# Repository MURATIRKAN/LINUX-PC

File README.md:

# LINUX-PC
DEBIAN İMAGE DOSYA:https://www.beagleboard.org/distros/am335x-debian-11-7-2023-08-05-4gb-emmc-iot-flasher
COUNTER STRIKE VE MINECRAFT APK ANDROID SÜRÜMLERİ İLE ÇALIŞIR.

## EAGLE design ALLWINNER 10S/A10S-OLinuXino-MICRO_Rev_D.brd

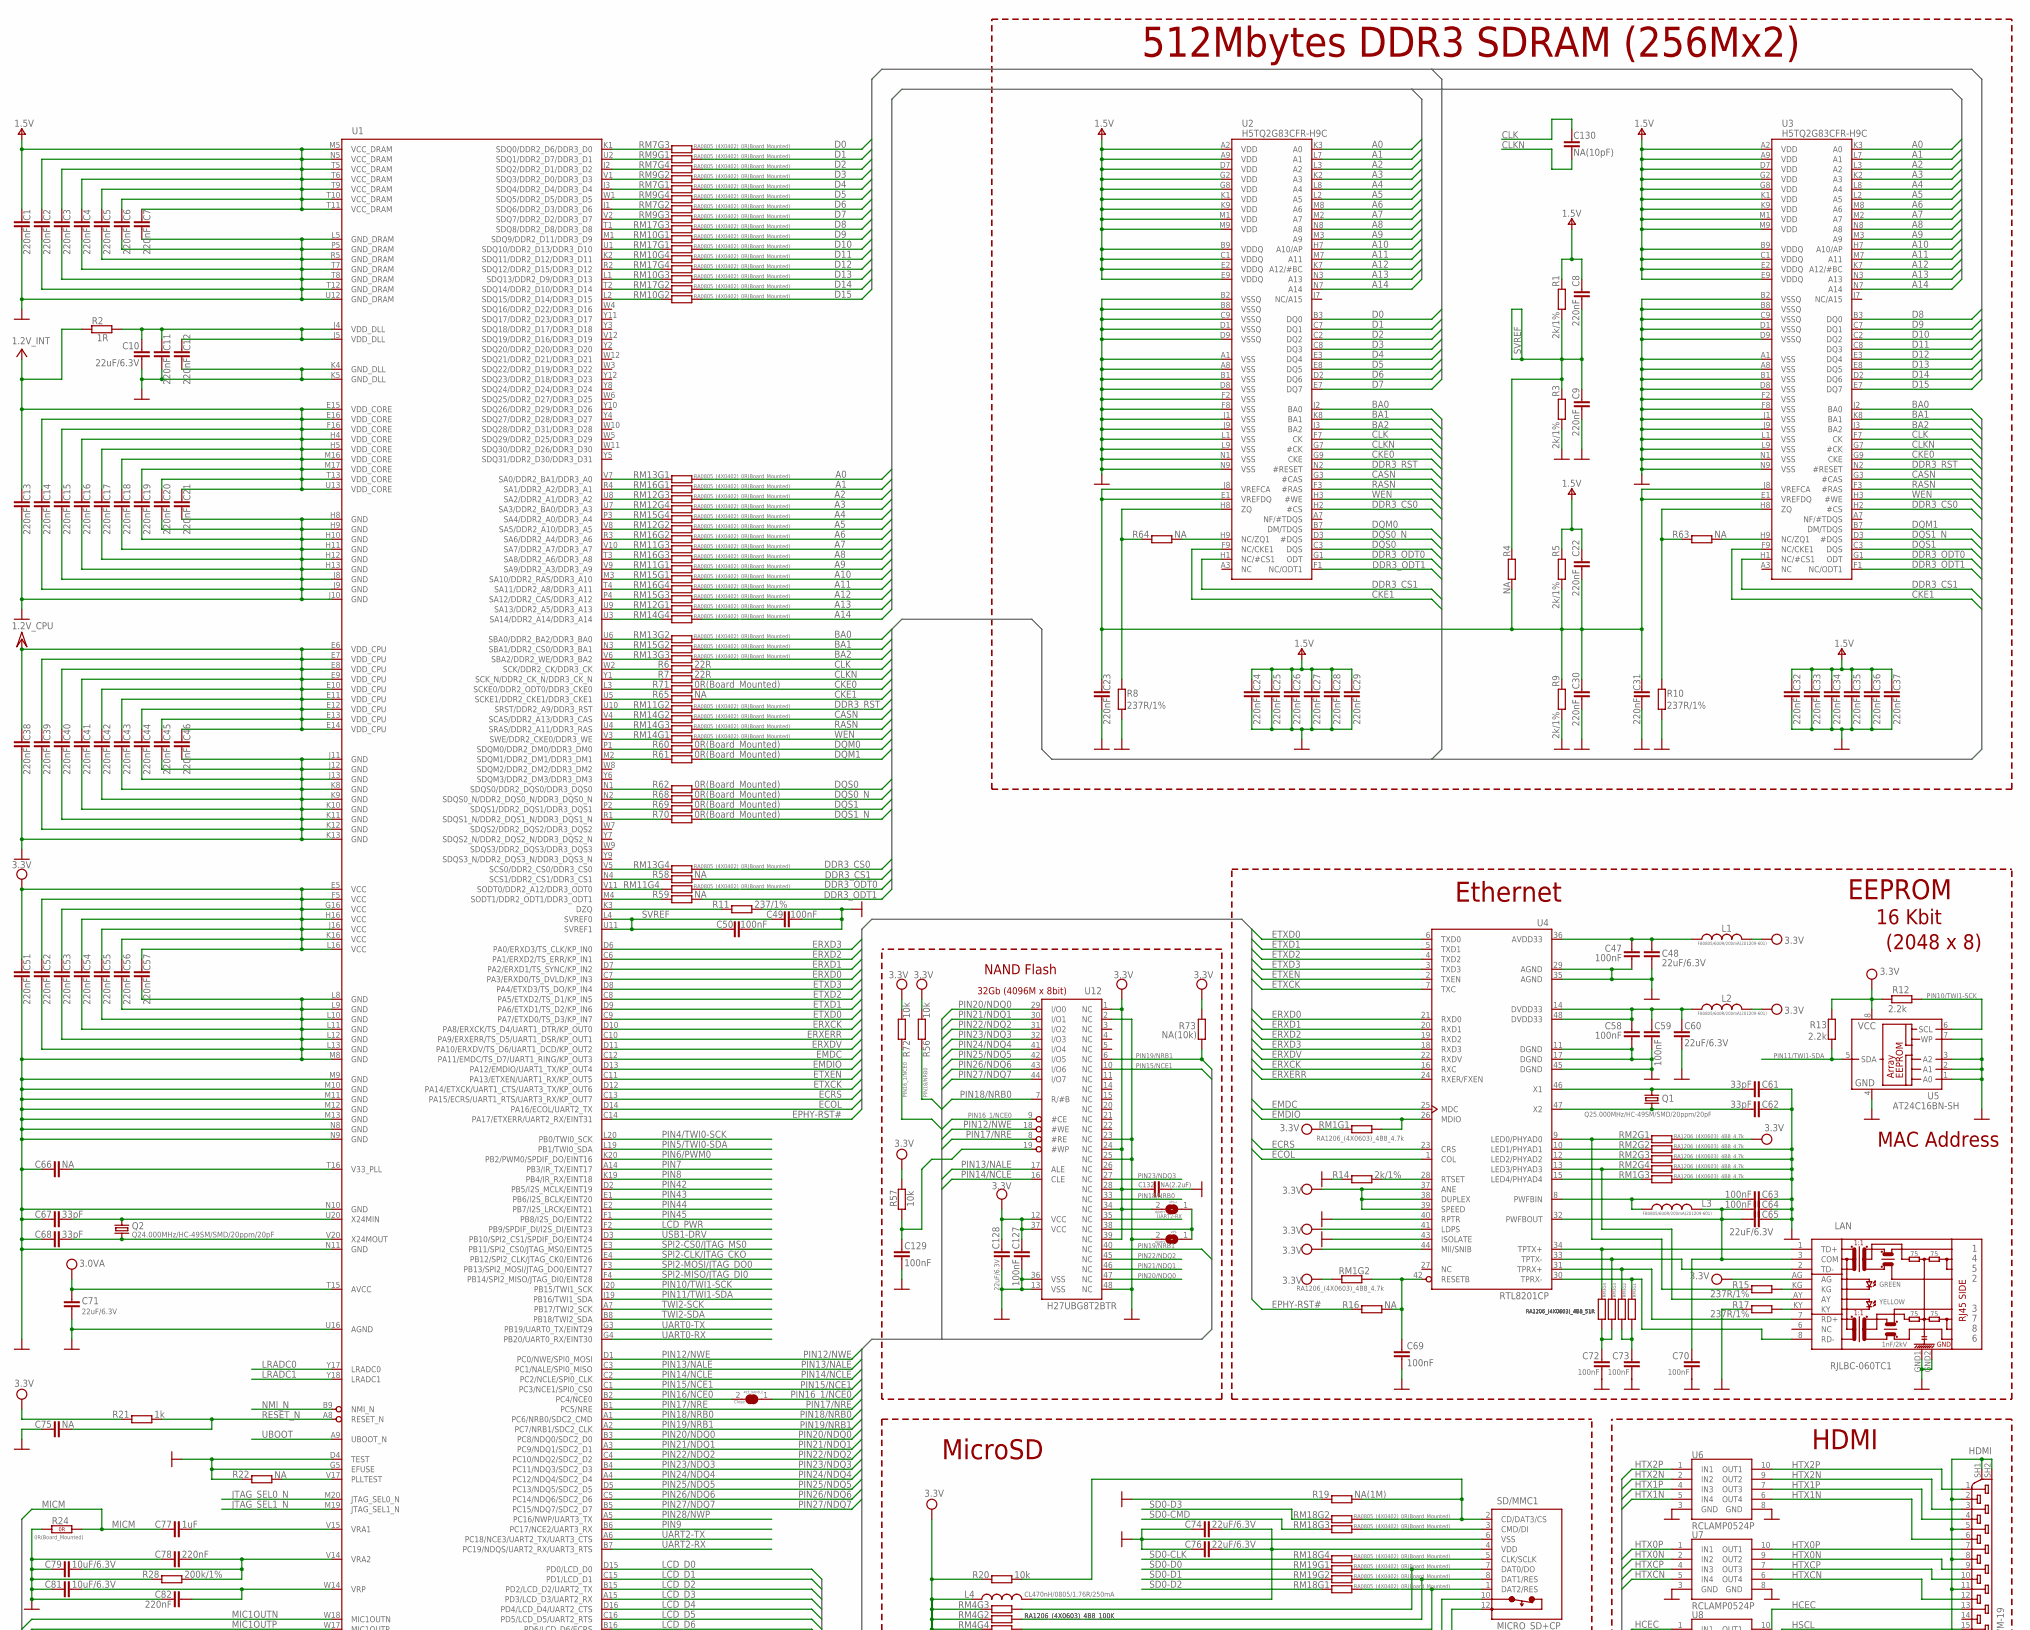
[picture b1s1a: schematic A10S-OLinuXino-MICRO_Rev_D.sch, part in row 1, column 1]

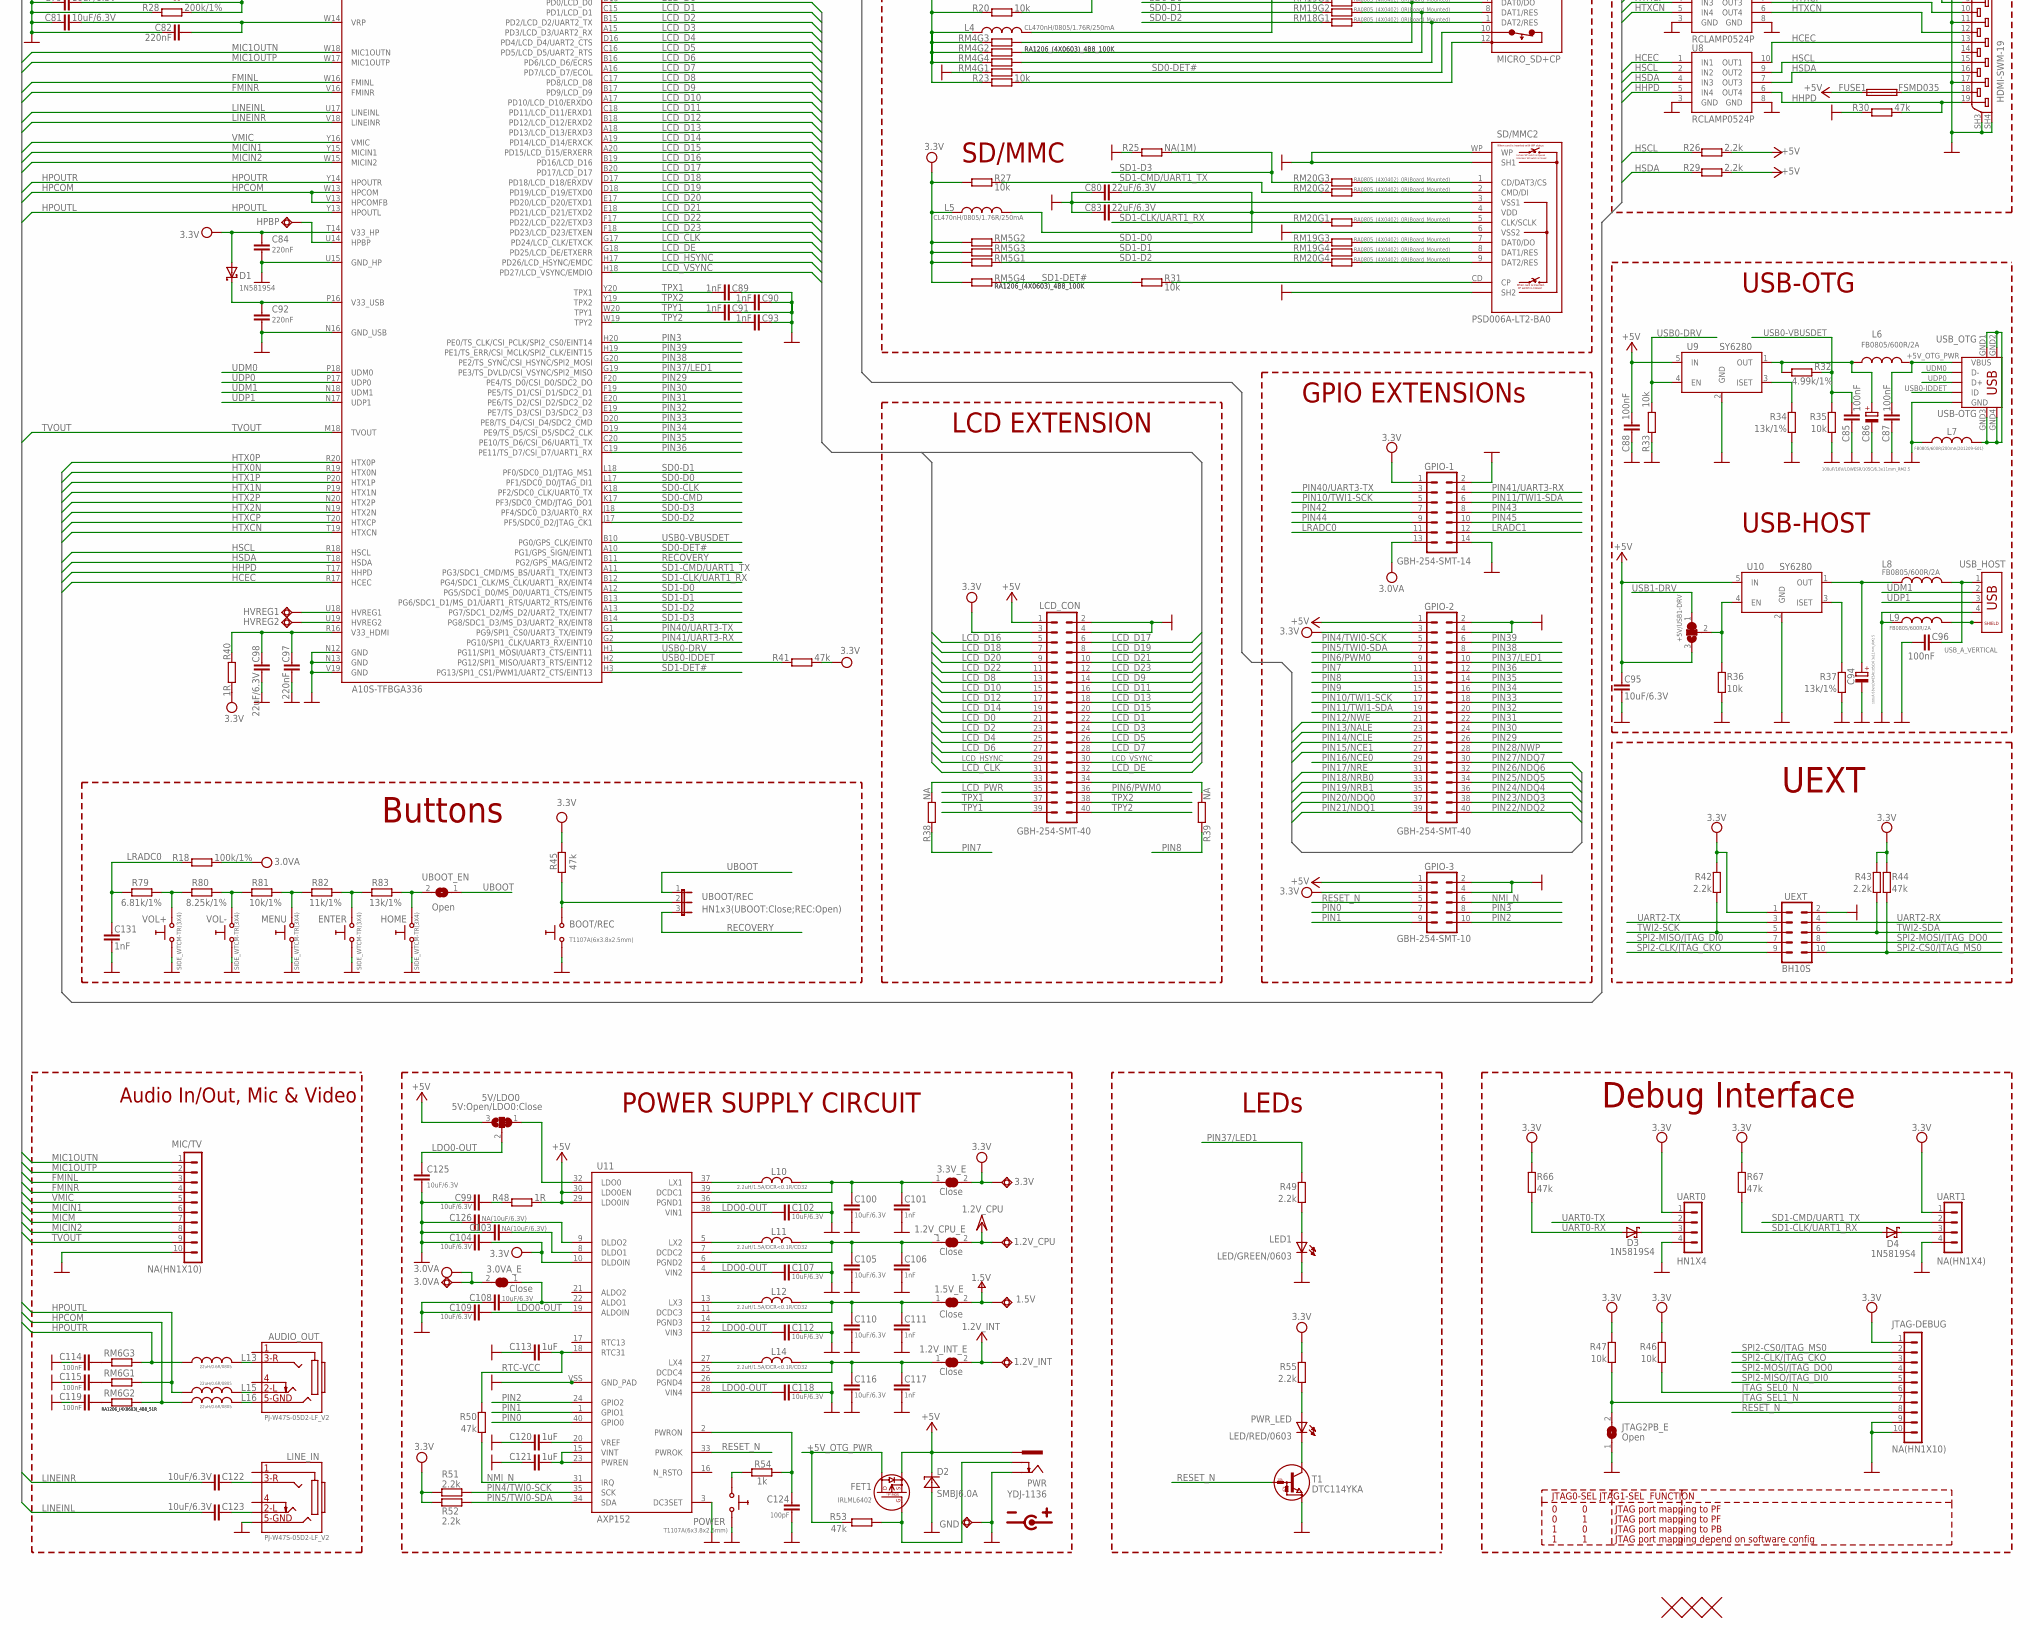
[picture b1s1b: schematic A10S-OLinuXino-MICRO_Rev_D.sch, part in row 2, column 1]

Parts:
1.2V_CPU, 1.2V_INT, 1.5V, 3.0VA, 3.3V: TESTPADTESTPAD_40-ROUND; TESTPAD_40-ROUND
1.2V_CPU_E, 1.2V_INT_E, 1.5V_E, 3.0VA_E, 3.3V_E: Close; SJ_1_SMALLER_CLOSE
5V/LDO0: 5V:Open/LDO0:Close; SJ_2_SMALL_12_TIED
#CE_NAND_E: Close; SJ_1_SMALLER_CLOSE
+5V/USB1-DRV: SJ2W4; SJ_2_SMALLER
AUDIO_OUT: PJ-W47S-05D2-LF_V2; PJ-W47S-05D2-LF_5PIN_V2
BOOT/REC: T1107A(6x3.8x2.5mm); SW-TAKT_6X3.5_SMD
C1, C2, C3, C4, C5, C6, C7, C11, C12, C13, C14, C15, C16, C17, C18, C19, C20, C21, C24, C32, C33, C34, C38, C39, C40, C41, C42, C43, C44, C45, C46, C51, C52, C53, C54, C55, C56, C57, C78, C82, C84, C92, C97: 220nF; C0402_TI
C8, C9, C22, C23, C25, C26, C27, C28, C29, C30, C31, C35, C36, C37: 220nF; C0603_DWS
C10, C48, C60, C65, C71, C74, C76, C80, C83, C98, C128: 22uF/6.3V; C0603_DWS
C47, C49, C50, C58, C59, C63, C64, C69, C70, C72, C73, C85, C87, C88, C96, C114, C115, C119, C127, C129: 100nF; C0603_DWS
C61, C62, C67, C68: 33pF; C0603_DWS
C66: NA; C0402_TI
C75: NA; C0603_DWS
C77, C113, C120, C121: 1uF; C0603_DWS
C79, C81, C95, C99, C100, C102, C104, C105, C107, C108, C109, C110, C112, C116, C118, C122, C123, C125: 10uF/6.3V; C0603_DWS
C86, C94: 100uF/16V/LOWESR/105C/6.3x11mm_RM2.5; E2,5-6,3
C89, C90, C91, C93, C101, C106, C111, C117, C131: 1nF; C0603_DWS
C103, C126: NA(10uF/6.3V); C0603_DWS
C124: 100pF; C0603_DWS
C130: NA(10pF); C0402_TI
C132: NA(2.2uF); C0603_DWS
D1, D3, D4: 1N5819S4; SOD-123
D2: SMBJ6.0A; DO214AA
ENTER: SIDE_WTCM-TR(3X4); SW_TAKT3X4
FET1: IRLML6402; SOT23
FUSE1: FSMD035; 1206
GND: TESTPADTESTPAD_40-ROUND; TESTPAD_40-ROUND
GPIO-1: GBH-254-SMT-14; ML14_S
GPIO-2: GBH-254-SMT-40; ML40-MALE(GBH-254-SMT-40)
GPIO-3: GBH-254-SMT-10; ML10_S
HDMI: HDMI-SWM-19
HOME: SIDE_WTCM-TR(3X4); SW_TAKT3X4
HPBP: TESTPADTESTPAD_40-ROUND; TESTPAD_40-ROUND
HVREG1, HVREG2: TESTPADTESTPAD_40-ROUND; TESTPAD_40-ROUND
JTAG2PB_E: Open; SJ_1_SMALLER
JTAG-DEBUG: NA(HN1X10); HN1X10
L1, L2, L3, L7: FB0805/600R/200mA(201209-601); L0805_5MIL_DWS
L4, L5: CL470nH/0805/1.76R/250mA; L0805_5MIL_DWS
L6, L8, L9: FB0805/600R/2A; L0805_5MIL_DWS
L10, L11, L12, L14: 2.2uH/1.5A/DCR<0.1R/CD32; CD32
L13, L15, L16: 22uH/0.6R/0805; L0805_5MIL_DWS
LAN: RJLBC-060TC1
LCD_CON: GBH-254-SMT-40; ML40-MALE(GBH-254-SMT-40)
LED1: LED/GREEN/0603; LED-0603
LINE_IN: PJ-W47S-05D2-LF_V2; PJ-W47S-05D2-LF_5PIN_V2
MENU: SIDE_WTCM-TR(3X4); SW_TAKT3X4
MIC/TV: NA(HN1X10); HN1X10
POWER: T1107A(6x3.8x2.5mm); SW-TAKT_6X3.5_SMD
PWR: YDJ-1136; PWR_JACK_UNI_MILLING
PWR_LED: LED/RED/0603; LED-0603
Q1: Q25.000MHz/HC-49SM/SMD/20ppm/20pF; HC49/SMD2_THIN
Q2: Q24.000MHz/HC-49SM/SMD/20ppm/20pF; HC49/SMD2_THIN
R1, R3, R5, R9, R14: 2k/1%; R0603_5MIL_DWS
R2, R40, R48: 1R; R0603_5MIL_DWS
R4, R16, R22, R38, R39, R63, R64: NA; R0603_5MIL_DWS
R6, R7: 22R; R0402_TI
R8, R10, R15, R17: 237R/1%; R0603_5MIL_DWS
R11: 237/1%; R0603_5MIL_DWS
R12, R13, R26, R29, R42, R43, R49, R51, R52, R55: 2.2k; R0603_5MIL_DWS
R18: 100k/1%; R0603_5MIL_DWS
R19, R25: NA(1M); R0603_5MIL_DWS
R20, R23, R27, R31, R33, R35, R36, R46, R47, R56, R57, R72: 10k; R0603_5MIL_DWS
R21, R54: 1k; R0603_5MIL_DWS
R24: 0R(Board_Mounted); 0603_0R
R28: 200k/1%; R0603_5MIL_DWS
R30, R41, R44, R45, R50, R53, R66, R67: 47k; R0603_5MIL_DWS
R32: 4.99k/1%; R0603_5MIL_DWS
R34, R37, R83: 13k/1%; R0603_5MIL_DWS
R58, R59, R65: NA; R0402_TI
R60, R61, R62, R68, R69, R70, R71: 0R(Board_Mounted); R0402_TI_0R
R73: NA(10k); R0603_5MIL_DWS
R79: 6.81k/1%; R0603_5MIL_DWS
R80: 8.25k/1%; R0603_5MIL_DWS
R81: 10k/1%; R0603_5MIL_DWS
R82: 11k/1%; R0603_5MIL_DWS
RM1, RM2: RA1206_(4X0603)_4B8_4.7k; R_MATRIX_4
RM3, RM6: RA1206_(4X0603)_4B8_51R; R_MATRIX_4
RM4, RM5: RA1206_(4X0603)_4B8_100K; R_MATRIX_4
RM7, RM9, RM10, RM11, RM12, RM13, RM14, RM15, RM16, RM17, RM18, RM19, RM20: RA0805_(4X0402)_0R(Board_Mounted); R_MATRIX_4_0402_25_625_0R
SD/MMC1: MICRO_SD+CP; TFR-MEM-CON
SD/MMC2: PSD006A-LT2-BA0; SD_CARD
T1: DTC114YKA; SOT-23
U1: A10S-TFBGA336; TFBGA336
U2, U3: H5TQ2G83CFR-H9C; FBGA78
U4: RTL8201CP; LQFP48
U5: AT24C16BN-SH; SO-08MN
U6, U7, U8: RCLAMP0524P; SLP2510P8
U9, U10: SY6280; SOT23-5
U11: AXP152; QFN40_5X5
U12: H27UBG8T2BTR; TSOP48
U15, U16, U17: FIDUCIAL1X2; FIDUCIAL-1X2
UART0: HN1X4
UART1: NA(HN1X4); HN1X4
UBOOT/REC: HN1x3(UBOOT:Close;REC:Open); JP2
UBOOT_EN: Open; SJ_1_SMALLER
UEXT: BH10S; ML10_S
USB_HOST: USB_A_VERTICAL; USB_A_VERTICAL_PTH
USB_OTG: USB-OTG; USB_MINI_9PIN
VOL+: SIDE_WTCM-TR(3X4); SW_TAKT3X4
VOL-: SIDE_WTCM-TR(3X4); SW_TAKT3X4
VPS+: open; SJ_1_THE_SMALLEST
VPS-: open; SJ_1_THE_SMALLEST

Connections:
+5V: 5V/LDO0.3, +5V/USB1-DRV.3, C88.1, C95.1, D2.C, FET1.2 (S), FUSE1.1, GPIO-2.1, GPIO-3.1, LCD_CON.1, PWR.+, R26.1, R29.1, R48.2, U9.5 (IN), U10.5 (IN), U11.29 (LDO0IN), U11.30 (LDO0EN)
+5V_OTG_PWR: C87.1, FET1.3 (D), L6.1, R53.2, USB_OTG.VBUS
A0: RM13.1.2 (2), U2.K3 (A0), U3.K3 (A0)
A1: RM16.1.2 (2), U2.L7 (A1), U3.L7 (A1)
A2: RM12.3.2 (2), U2.L3 (A2), U3.L3 (A2)
A3: RM12.4.2 (2), U2.K2 (A3), U3.K2 (A3)
A4: RM15.4.2 (2), U2.L8 (A4), U3.L8 (A4)
A5: RM12.2.2 (2), U2.L2 (A5), U3.L2 (A5)
A6: RM16.2.2 (2), U2.M8 (A6), U3.M8 (A6)
A7: RM11.3.1 (1), U2.M2 (A7), U3.M2 (A7)
A8: RM16.3.2 (2), U2.N8 (A8), U3.N8 (A8)
A9: RM11.1.1 (1), U2.M3 (A9), U3.M3 (A9)
A10: RM15.1.2 (2), U2.H7 (A10/AP), U3.H7 (A10/AP)
A11: RM16.4.2 (2), U2.M7 (A11), U3.M7 (A11)
A12: RM15.3.2 (2), U2.K7 (A12/#BC), U3.K7 (A12/#BC)
A13: RM12.1.2 (2), U2.N3 (A13), U3.N3 (A13)
A14: RM14.4.2 (2), U2.N7 (A14), U3.N7 (A14)
AVDD33: C47.2, C48.2, L1.1, U4.36 (AVDD33)
BA0: RM13.2.2 (2), U2.J2 (BA0), U3.J2 (BA0)
BA1: RM15.2.2 (2), U2.K8 (BA1), U3.K8 (BA1)
BA2: RM13.3.2 (2), U2.J3 (BA2), U3.J3 (BA2)
CASN: RM14.2.2 (2), U2.G3 (#CAS), U3.G3 (#CAS)
CKE0: R71.1, U2.G9 (CKE), U3.G9 (CKE)
CKE1: R65.1, U2.F9 (NC/CKE1), U3.F9 (NC/CKE1)
CLK: C130.2, R6.1, U2.F7 (CK), U3.F7 (CK)
CLKN: C130.1, R7.1, U2.G7 (#CK), U3.G7 (#CK)
CS0: RM13.4.1 (1), U1.V5 (SCS0/DDR2_CS0/DDR3_CS0)
CS1: R58.2, U1.N4 (SCS1/DDR2_CS1/DDR3_CS1)
D0: RM7.3.2 (2), U2.B3 (DQ0)
D1: RM9.1.2 (2), U2.C7 (DQ1)
D2: RM7.4.2 (2), U2.C2 (DQ2)
D3: RM9.2.2 (2), U2.C8 (DQ3)
D4: RM7.1.2 (2), U2.E3 (DQ4)
D5: RM9.4.2 (2), U2.E8 (DQ5)
D6: RM7.2.2 (2), U2.D2 (DQ6)
D7: RM9.3.2 (2), U2.E7 (DQ7)
D8: RM17.3.2 (2), U3.B3 (DQ0)
D9: RM10.1.2 (2), U3.C7 (DQ1)
D10: RM17.1.2 (2), U3.C2 (DQ2)
D11: RM10.4.2 (2), U3.C8 (DQ3)
D12: RM17.4.2 (2), U3.E3 (DQ4)
D13: RM10.3.2 (2), U3.E8 (DQ5)
D14: RM17.2.2 (2), U3.D2 (DQ6)
D15: RM10.2.2 (2), U3.E7 (DQ7)
DDR3_A0: RM13.1.1 (1), U1.V7 (SA0/DDR2_BA1/DDR3_A0)
DDR3_A1: RM16.1.1 (1), U1.R4 (SA1/DDR2_A2/DDR3_A1)
DDR3_A2: RM12.3.1 (1), U1.U8 (SA2/DDR2_A1/DDR3_A2)
DDR3_A3: RM12.4.1 (1), U1.U7 (SA3/DDR2_BA0/DDR3_A3)
DDR3_A4: RM15.4.1 (1), U1.P3 (SA4/DDR2_A0/DDR3_A4)
DDR3_A5: RM12.2.1 (1), U1.V8 (SA5/DDR2_A10/DDR3_A5)
DDR3_A6: RM16.2.1 (1), U1.R3 (SA6/DDR2_A4/DDR3_A6)
DDR3_A7: RM11.3.2 (2), U1.V10 (SA7/DDR2_A7/DDR3_A7)
DDR3_A8: RM16.3.1 (1), U1.T3 (SA8/DDR2_A6/DDR3_A8)
DDR3_A9: RM11.1.2 (2), U1.V9 (SA9/DDR2_A3/DDR3_A9)
DDR3_A10: RM15.1.1 (1), U1.M3 (SA10/DDR2_RAS/DDR3_A10)
DDR3_A11: RM16.4.1 (1), U1.T4 (SA11/DDR2_A8/DDR3_A11)
DDR3_A12: RM15.3.1 (1), U1.P4 (SA12/DDR2_CAS/DDR3_A12)
DDR3_A13: RM12.1.1 (1), U1.U9 (SA13/DDR2_A5/DDR3_A13)
DDR3_A14: RM14.4.1 (1), U1.U3 (SA14/DDR2_A14/DDR3_A14)
DDR3_BA0: RM13.2.1 (1), U1.U6 (SBA0/DDR2_BA2/DDR3_BA0)
DDR3_BA1: RM15.2.1 (1), U1.N3 (SBA1/DDR2_CS0/DDR3_BA1)
DDR3_BA2: RM13.3.1 (1), U1.V6 (SBA2/DDR2_WE/DDR3_BA2)
DDR3_CAS: RM14.2.1 (1), U1.V4 (SCAS/DDR2_A13/DDR3_CAS)
DDR3_CKE0: R71.2, U1.L3 (SCKE0/DDR2_ODT0/DDR3_CKE0)
DDR3_CKE1: R65.2, U1.U5 (SCKE1/DDR2_CKE1/DDR3_CKE1)
DDR3_CLK: R6.2, U1.W2 (SCK/DDR2_CK/DDR3_CK)
DDR3_CLKN: R7.2, U1.Y1 (SCK_N/DDR2_CK_N/DDR3_CK_N)
DDR3_CS0: RM13.4.2 (2), U2.H2 (#CS), U3.H2 (#CS)
DDR3_CS1: R58.1, U2.H1 (NC/#CS1), U3.H1 (NC/#CS1)
DDR3_D0: RM7.3.1 (1), U1.K1 (SDQ0/DDR2_D6/DDR3_D0)
DDR3_D1: RM9.1.1 (1), U1.U2 (SDQ1/DDR2_D7/DDR3_D1)
DDR3_D2: RM7.4.1 (1), U1.J2 (SDQ2/DDR2_D1/DDR3_D2)
DDR3_D3: RM9.2.1 (1), U1.V1 (SDQ3/DDR2_D0/DDR3_D3)
DDR3_D4: RM7.1.1 (1), U1.J3 (SDQ4/DDR2_D4/DDR3_D4)
DDR3_D5: RM9.4.1 (1), U1.W1 (SDQ5/DDR2_D5/DDR3_D5)
DDR3_D6: RM7.2.1 (1), U1.J1 (SDQ6/DDR2_D3/DDR3_D6)
DDR3_D7: RM9.3.1 (1), U1.V2 (SDQ7/DDR2_D2/DDR3_D7)
DDR3_D8: RM17.3.1 (1), U1.T1 (SDQ8/DDR2_D8/DDR3_D8)
DDR3_D9: RM10.1.1 (1), U1.M1 (SDQ9/DDR2_D11/DDR3_D9)
DDR3_D10: RM17.1.1 (1), U1.U1 (SDQ10/DDR2_D13/DDR3_D10)
DDR3_D11: RM10.4.1 (1), U1.K2 (SDQ11/DDR2_D12/DDR3_D11)
DDR3_D12: RM17.4.1 (1), U1.R2 (SDQ12/DDR2_D15/DDR3_D12)
DDR3_D13: RM10.3.1 (1), U1.L1 (SDQ13/DDR2_D9/DDR3_D13)
DDR3_D14: RM17.2.1 (1), U1.T2 (SDQ14/DDR2_D10/DDR3_D14)
DDR3_D15: RM10.2.1 (1), U1.L2 (SDQ15/DDR2_D14/DDR3_D15)
DDR3_DQM0: R60.2, U1.P1 (SDQM0/DDR2_DM0/DDR3_DM0)
DDR3_DQM1: R61.2, U1.M2 (SDQM1/DDR2_DM1/DDR3_DM1)
DDR3_DQS0: R62.2, U1.N1 (SDQS0/DDR2_DQS0/DDR3_DQS0)
DDR3_DQS0_N: R68.2, U1.N2 (SDQS0_N/DDR2_DQS0_N/DDR3_DQS0_N)
DDR3_DQS1: R69.2, U1.P2 (SDQS1/DDR2_DQS1/DDR3_DQS1)
DDR3_DQS1_N: R70.2, U1.R1 (SDQS1_N/DDR2_DQS1_N/DDR3_DQS1_N)
DDR3_ODT0: RM11.4.1 (1), U2.G1 (ODT), U3.G1 (ODT)
DDR3_ODT1: R59.1, U2.F1 (NC/ODT1), U3.F1 (NC/ODT1)
DDR3_RAS: RM14.3.1 (1), U1.U4 (SRAS/DDR2_A11/DDR3_RAS)
DDR3_RST: RM11.2.1 (1), U2.N2 (#RESET), U3.N2 (#RESET)
DDR3_RSTT: RM11.2.2 (2), U1.U10 (SRST/DDR2_A9/DDR3_RST)
DDR3_WE: RM14.1.1 (1), U1.V3 (SWE/DDR2_CKE0/DDR3_WE)
DQM0: R60.1, U2.B7 (DM/TDQS)
DQM1: R61.1, U3.B7 (DM/TDQS)
DQS0: R62.1, U2.C3 (DQS)
DQS0_N: R68.1, U2.D3 (#DQS)
DQS1: R69.1, U3.C3 (DQS)
DQS1_N: R70.1, U3.D3 (#DQS)
DRAM-REF: C22.2, C23.2, C30.2, C31.2, R4.1, R5.1, R9.2, U2.E1 (VREFDQ), U2.J8 (VREFCA), U3.E1 (VREFDQ), U3.J8 (VREFCA)
DVDD33: C58.2, C59.2, C60.2, L2.1, U4.14 (DVDD33), U4.48 (DVDD33)
DZQ: R11.2, U1.K3 (DZQ)
ECOL: U1.D14 (PA16/ECOL/UART2_TX), U4.1 (COL)
ECRS: U1.C13 (PA15/ECRS/UART1_RTS/UART3_RX/KP_OUT7), U4.23 (CRS)
EMDC: U1.C12 (PA11/EMDC/TS_D7/UART1_RING/KP_OUT3), U4.25 (MDC)
EMDIO: RM1.1.2 (2), U1.D13 (PA12/EMDIO/UART1_TX/KP_OUT4), U4.26 (MDIO)
EPHY-RST#: R16.1, U1.C14 (PA17/ETXERR/UART2_RX/EINT31)
ERXCK: U1.D10 (PA8/ERXCK/TS_D4/UART1_DTR/KP_OUT0), U4.16 (RXC)
ERXD0: U1.C7 (PA3/ERXD0/TS_DVLD/KP_IN3), U4.21 (RXD0)
ERXD1: U1.D7 (PA2/ERXD1/TS_SYNC/KP_IN2), U4.20 (RXD1)
ERXD2: U1.C6 (PA1/ERXD2/TS_ERR/KP_IN1), U4.19 (RXD2)
ERXD3: U1.D6 (PA0/ERXD3/TS_CLK/KP_IN0), U4.18 (RXD3)
ERXDV: U1.D11 (PA10/ERXDV/TS_D6/UART1_DCD/KP_OUT2), U4.22 (RXDV)
ERXERR: U1.C10 (PA9/ERXERR/TS_D5/UART1_DSR/KP_OUT1), U4.24 (RXER/FXEN)
ETXCK: U1.D12 (PA14/ETXCK/UART1_CTS/UART3_TX/KP_OUT6), U4.7 (TXC)
ETXD0: U1.C9 (PA7/ETXD0/TS_D3/KP_IN7), U4.6 (TXD0)
ETXD1: U1.D9 (PA6/ETXD1/TS_D2/KP_IN6), U4.5 (TXD1)
ETXD2: U1.C8 (PA5/ETXD2/TS_D1/KP_IN5), U4.4 (TXD2)
ETXD3: U1.D8 (PA4/ETXD3/TS_DO/KP_IN4), U4.3 (TXD3)
ETXEN: U1.C11 (PA13/ETXEN/UART1_RX/KP_OUT5), U4.2 (TXEN)
FMINL: MIC/TV.3, U1.W16 (FMINL)
FMINR: MIC/TV.4, U1.V16 (FMINR)
GND: BOOT/REC.P$1 (0), C1.1, C2.1, C3.1, C4.1, C5.1, C6.1, C7.1, C9.1, C10.1, C11.1, C12.1, C13.1, C14.1, C15.1, C16.1, C17.1, C18.1, C19.1, C20.1, C21.1, C23.1, C24.1, C25.1, C26.1, C27.1, C28.1, C29.1, C30.1, C31.1, C32.1, C33.1, C34.1, C35.1, C36.1, C37.1, C38.1, C39.1, C40.1, C41.1, C42.1, C43.1, C44.1, C45.1, C46.1, C47.1, C48.1, C49.1, C50.1, C51.1, C52.1, C53.1, C54.1, C55.1, C56.1, C57.1, C58.1, C59.1, C60.1, C61.1, C62.1, C63.2, C64.2, C65.2, C66.1, C67.1, C68.1, C69.1, C70.1, C71.1, C72.1, C73.1, C74.1, C75.1, C76.1, C78.1, C79.1, C80.1, C81.1, C82.1, C83.1, C84.1, C85.2, C86.-, C87.2, C88.2, C89.1, C90.1, C91.1, C92.1, C93.1, C94.-, C95.2, C96.2, C97.2, C98.1, C99.2, C100.2, C101.2, C102.2, C103.2, C104.2, C105.2, C106.2, C107.2, C108.2, C109.2, C110.2, C111.2, C112.2, C113.2, C114.1, C115.1, C116.2, C117.2, C118.2, C119.1, C120.2, C121.2, C124.2, C125.2, C126.2, C127.1, C128.1, C129.1, C131.2, C132.1, D2.A, ENTER.2_1 (0), GND.1, GPIO-1.2, GPIO-1.14, GPIO-2.2, GPIO-2.4, GPIO-3.2, GPIO-3.4, HDMI.2, HDMI.5, HDMI.8, HDMI.11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
HCEC: HDMI.13, U1.R17 (HCEC), U8.1 (IN1), U8.10 (OUT1)
HDMI_5V_SOURCE: FUSE1.2, HDMI.18
HHPD: HDMI.19, R30.1, U1.T17 (HHPD), U8.5 (IN4), U8.6 (OUT4)
HPCOM: L16.1, RM6.2.2 (2), U1.V13 (HPCOMFB), U1.W13 (HPCOM)
HPOUTL: L15.1, RM6.1.2 (2), U1.Y13 (HPOUTL)
HPOUTR: L13.1, RM6.3.2 (2), U1.Y14 (HPOUTR)
HSCL: HDMI.15, R26.2, U1.R18 (HSCL), U8.2 (IN2), U8.9 (OUT2)
HSDA: HDMI.16, R29.2, U1.T18 (HSDA), U8.4 (IN3), U8.7 (OUT3)
HTX0N: HDMI.9, U1.R19 (HTX0N), U7.2 (IN2), U7.9 (OUT2)
HTX0P: HDMI.7, U1.R20 (HTX0P), U7.1 (IN1), U7.10 (OUT1)
HTX1N: HDMI.6, U1.P19 (HTX1N), U6.5 (IN4), U6.6 (OUT4)
HTX1P: HDMI.4, U1.P20 (HTX1P), U6.4 (IN3), U6.7 (OUT3)
HTX2N: HDMI.3, U1.N19 (HTX2N), U6.2 (IN2), U6.9 (OUT2)
HTX2P: HDMI.1, U1.N20 (HTX2P), U6.1 (IN1), U6.10 (OUT1)
HTXCN: HDMI.12, U1.T19 (HTXCN), U7.5 (IN4), U7.6 (OUT4)
HTXCP: HDMI.10, U1.T20 (HTXCP), U7.4 (IN3), U7.7 (OUT3)
JTAG_SEL0_N: JTAG-DEBUG.6, R46.1, U1.M20 (JTAG_SEL0_N)
JTAG_SEL1_N: JTAG2PB_E.2, JTAG-DEBUG.7, R47.1, U1.M19 (JTAG_SEL1_N)
LCD_CLK: LCD_CON.31, U1.G17 (PD24/LCD_CLK/ETXCK)
LCD_D0: LCD_CON.21, U1.D15 (PD0/LCD_D0)
LCD_D1: LCD_CON.22, U1.C15 (PD1/LCD_D1)
LCD_D2: LCD_CON.23, U1.B15 (PD2/LCD_D2/UART2_TX)
LCD_D3: LCD_CON.24, U1.A15 (PD3/LCD_D3/UART2_RX)
LCD_D4: LCD_CON.25, U1.D16 (PD4/LCD_D4/UART2_CTS)
LCD_D5: LCD_CON.26, U1.C16 (PD5/LCD_D5/UART2_RTS)
LCD_D6: LCD_CON.27, U1.B16 (PD6/LCD_D6/ECRS)
LCD_D7: LCD_CON.28, U1.A16 (PD7/LCD_D7/ECOL)
LCD_D8: LCD_CON.13, U1.C17 (PD8/LCD_D8)
LCD_D9: LCD_CON.14, U1.B17 (PD9/LCD_D9)
LCD_D10: LCD_CON.15, U1.A17 (PD10/LCD_D10/ERXDO)
LCD_D11: LCD_CON.16, U1.C18 (PD11/LCD_D11/ERXD1)
LCD_D12: LCD_CON.17, U1.B18 (PD12/LCD_D12/ERXD2)
LCD_D13: LCD_CON.18, U1.A18 (PD13/LCD_D13/ERXD3)
LCD_D14: LCD_CON.19, U1.A19 (PD14/LCD_D14/ERXCK)
LCD_D15: LCD_CON.20, U1.A20 (PD15/LCD_D15/ERXERR)
LCD_D16: LCD_CON.5, U1.B19 (PD16/LCD_D16)
LCD_D17: LCD_CON.6, U1.B20 (PD17/LCD_D17)
LCD_D18: LCD_CON.7, U1.D17 (PD18/LCD_D18/ERXDV)
LCD_D19: LCD_CON.8, U1.D18 (PD19/LCD_D19/ETXD0)
LCD_D20: LCD_CON.9, U1.E17 (PD20/LCD_D20/ETXD1)
LCD_D21: LCD_CON.10, U1.E18 (PD21/LCD_D21/ETXD2)
LCD_D22: LCD_CON.11, U1.F17 (PD22/LCD_D22/ETXD3)
LCD_D23: LCD_CON.12, U1.F18 (PD23/LCD_D23/ETXEN)
LCD_DE: LCD_CON.32, U1.G18 (PD25/LCD_DE/ETXERR)
LCD_HSYNC: LCD_CON.29, U1.H17 (PD26/LCD_HSYNC/EMDC)
LCD_PWR: LCD_CON.35, U1.F2 (PB9/SPDIF_DI/I2S_DI/EINT23)
LCD_VSYNC: LCD_CON.30, U1.H18 (PD27/LCD_VSYNC/EMDIO)
LDO0-OUT: 5V/LDO0.2, C102.1, C107.1, C109.1, C112.1, C118.1, C125.1, U11.4 (VIN2), U11.12 (VIN3), U11.19 (ALDOIN), U11.28 (VIN4), U11.38 (VIN1)
LINEINL: C123.2, U1.U17 (LINEINL)
LINEINR: C122.2, U1.V18 (LINEINR)
LRADC0: C131.1, GPIO-1.11, R18.2, R79.1, U1.Y17 (LRADC0)
LRADC1: GPIO-1.12, U1.Y18 (LRADC1)
MIC1OUTN: MIC/TV.1, U1.W18 (MIC1OUTN)
MIC1OUTP: MIC/TV.2, U1.W17 (MIC1OUTP)
MICIN1: MIC/TV.6, U1.Y15 (MICIN1)
MICIN2: MIC/TV.8, U1.W15 (MICIN2)
MICM: C77.1, MIC/TV.7, R24.2 (1.2)
unnamed: R22.1, U1.V17 (PLLTEST)
unnamed: HVREG1.1, U1.U18 (HVREG1)
unnamed: R8.2, R64.1, U2.H8 (ZQ)
unnamed: HVREG2.1, U1.U19 (HVREG2)
unnamed: R10.2, R63.1, U3.H8 (ZQ)
unnamed: R14.2, U4.28 (RTSET)
unnamed: HPBP.1, U1.U14 (HPBP)
unnamed: C121.1, U11.15 (VINT), U11.23 (PWREN)
unnamed: C122.1, LINE_IN.3
unnamed: 3.0VA_E.1, C108.1, U11.22 (ALDO1)
unnamed: C66.2, U1.T16 (V33_PLL)
unnamed: RM1.3.1 (1), U4.15 (LED4/PHYAD4)
unnamed: C123.1, LINE_IN.2
unnamed: POWER.P$1 (0), R54.2
unnamed: C126.1, U11.9 (DLDO2)
unnamed: PWR_LED.C, T1.3 (C)
unnamed: PWR_LED.A, R55.2
unnamed: C120.1, U11.20 (VREF)
unnamed: FET1.1 (G), PWR.--, R53.1
unnamed: 5V/LDO0.1, U11.32 (LDO0)
unnamed: +5V/USB1-DRV.2, R36.2, U10.4 (EN)
unnamed: AUDIO_OUT.5, L16.2
unnamed: C103.1, U11.8 (DLDO1)
unnamed: R79.2, R80.1, VOL+.1_1 (1)
unnamed: AUDIO_OUT.2, L15.2
unnamed: AUDIO_OUT.3, L13.2
unnamed: C92.2, D1.C, U1.P16 (V33_USB)
unnamed: HOME.1_1 (1), R83.2, UBOOT_EN.2
unnamed: RM4.4.1 (1), RM18.1.1 (1), SD/MMC1.1 (DAT2/RES)
unnamed: U12.38 (NC), VPS+.1, VPS-.1
unnamed: C69.2, R16.2, RM1.2.2 (2), U4.42 (RESETB)
unnamed: C73.2, RM3.1.1 (1), RM3.2.1 (1)
unnamed: C115.2, RM6.1.1 (1)
unnamed: C119.2, RM6.2.1 (1)
unnamed: R63.2, U3.H9 (NC/ZQ1)
unnamed: R64.2, U2.H9 (NC/ZQ1)
unnamed: D3.C, UART0.3
unnamed: LAN.1 (TD+), RM3.4.2 (2), U4.34 (TPTX+)
unnamed: LAN.2 (TD-), RM3.3.2 (2), U4.33 (TPTX-)
unnamed: LAN.7 (RD+), RM3.2.2 (2), U4.31 (TPRX+)
unnamed: RM18.3.1 (1), SD/MMC1.3 (CMD/DI)
unnamed: RM18.4.1 (1), SD/MMC1.5 (CLK/SCLK)
unnamed: C114.2, RM6.3.1 (1)
unnamed: LAN.8 (RD-), RM3.1.2 (2), U4.30 (TPRX-)
unnamed: RM4.3.1 (1), RM19.1.1 (1), SD/MMC1.7 (DAT0/DO)
unnamed: C72.2, RM3.3.1 (1), RM3.4.1 (1)
unnamed: L10.1, U11.37 (LX1)
unnamed: RM2.2.2 (2), U4.10 (LED1/PHYAD1)
unnamed: RM4.2.1 (1), RM19.2.1 (1), SD/MMC1.8 (DAT1/RES)
unnamed: RM2.3.2 (2), U4.12 (LED2/PHYAD2)
unnamed: RM20.3.1 (1), SD/MMC2.1 (CD/DAT3/CS)
unnamed: LAN.KG, R15.1
unnamed: LAN.AY, RM2.4.2 (2), U4.13 (LED3/PHYAD3)
unnamed: C63.1, L3.1, U4.8 (PWFBIN)
unnamed: C64.1, C65.1, C70.2, L3.2, LAN.3 (COM), U4.32 (PWFBOUT)
unnamed: LAN.KY, R17.1
unnamed: R23.1, SD/MMC1.12 (PACK)
unnamed: RM20.2.1 (1), SD/MMC2.2 (CMD/DI)
unnamed: RM20.1.1 (1), SD/MMC2.5 (CLK/SCLK)
unnamed: RM19.3.2 (2), SD/MMC2.7 (DAT0/DO)
unnamed: RM19.4.2 (2), SD/MMC2.8 (DAT1/RES)
unnamed: 3.3V_E.1, C100.1, C101.1, L10.2, U11.39 (DCDC1)
unnamed: C99.1, R48.1
unnamed: RM20.4.1 (1), SD/MMC2.9 (DAT2/RES)
unnamed: D4.C, UART1.3
unnamed: R15.2, RM2.1.2 (2), U4.9 (LED0/PHYAD0)
unnamed: L11.1, U11.5 (LX2)
unnamed: 1.2V_CPU_E.1, C105.1, C106.1, L11.2, U11.7 (DCDC2)
unnamed: L12.1, U11.13 (LX3)
unnamed: 1.5V_E.1, C110.1, C111.1, L12.2, U11.11 (DCDC3)
unnamed: L14.1, U11.27 (LX4)
unnamed: 1.2V_INT_E.1, C116.1, C117.1, L14.2, U11.25 (DCDC4)
unnamed: R19.1, R20.1, RM18.2.1 (1), SD/MMC1.2 (CD/DAT3/CS)
unnamed: BOOT/REC.P$2 (1), R45.2, UBOOT/REC.2
unnamed: R80.2, R81.1, VOL-.1_1 (1)
unnamed: MENU.1_1 (1), R81.2, R82.1
unnamed: ENTER.1_1 (1), R82.2, R83.1
unnamed: R34.2, U9.3 (ISET)
unnamed: C86.+, L6.2, R32.2, U9.1 (OUT)
unnamed: R37.2, U10.3 (ISET)
unnamed: L9.2, USB_HOST.P$3 (5), USB_HOST.P$4 (6)
unnamed: C96.1, L8.2, USB_HOST.1
unnamed: C81.2, C82.2, U1.W14 (VRP)
unnamed: C129.2, R57.2, U12.19 (#WP)
unnamed: C77.2, U1.V15 (VRA1)
unnamed: R31.1, SD/MMC2.CD (CP)
unnamed: C78.2, C79.2, R28.1, U1.V14 (VRA2)
unnamed: C94.+, L8.1, U10.1 (OUT)
unnamed: LCD_CON.33, R38.1
unnamed: LCD_CON.34, R39.1
unnamed: LED1.A, R49.2
unnamed: L7.2, USB_OTG.GND1, USB_OTG.GND2, USB_OTG.GND3, USB_OTG.GND4
NMI_N: GPIO-3.6, R50.1, U1.B9 (NMI_N), U11.31 (IRQ)
ODT0: RM11.4.2 (2), U1.V11 (SODT0/DDR2_A12/DDR3_ODT0)
ODT1: R59.2, U1.M4 (SODT1/DDR2_ODT1/DDR3_ODT1)
PIN0: GPIO-3.7, U11.40 (GPIO0)
PIN1: GPIO-3.9, U11.1 (GPIO1)
PIN2: GPIO-3.10, U11.24 (GPIO2)
PIN3: GPIO-3.8, U1.H20 (PE0/TS_CLK/CSI_PCLK/SPI2_CS0/EINT14)
PIN4/TWI0-SCK: GPIO-2.5, R51.1, U1.L20 (PB0/TWI0_SCK), U11.35 (SCK)
PIN5/TWI0-SDA: GPIO-2.7, R52.1, U1.L19 (PB1/TWI0_SDA), U11.34 (SDA)
PIN6/PWM0: GPIO-2.9, LCD_CON.36, U1.K20 (PB2/PWM0/SPDIF_DO/EINT16)
PIN7: GPIO-2.11, R38.2, U1.A14 (PB3/IR_TX/EINT17)
PIN8: GPIO-2.13, R39.2, U1.K19 (PB4/IR_RX/EINT18)
PIN9: GPIO-2.15, U1.B6 (PC17/NCE2/UART3_RX)
PIN10/TWI1-SCK: GPIO-1.5, GPIO-2.17, R12.2, U1.J20 (PB15/TWI1_SCK), U5.6 (SCL)
PIN11/TWI1-SDA: GPIO-1.6, GPIO-2.19, R13.1, U1.J19 (PB16/TWI1_SDA), U5.5 (SDA)
PIN12/NWE: GPIO-2.21, U1.D1 (PC0/NWE/SPI0_MOSI), U12.18 (#WE)
PIN13/NALE: GPIO-2.23, U1.C3 (PC1/NALE/SPI0_MISO), U12.17 (ALE)
PIN14/NCLE: GPIO-2.25, U1.C2 (PC2/NCLE/SPI0_CLK), U12.16 (CLE)
PIN15/NCE1: GPIO-2.27, U1.C1 (PC3/NCE1/SPI0_CS0), U12.10 (NC)
PIN16/NCE0: #CE_NAND_E.2, GPIO-2.29, U1.B2 (PC4/NCE0)
PIN16_1/NCE0: #CE_NAND_E.1, R72.2, U12.9 (#CE)
PIN17/NRE: GPIO-2.31, U1.B1 (PC5/NRE), U12.8 (#RE)
PIN18/NRB0: GPIO-2.33, R56.2, U1.A1 (PC6/NRB0/SDC2_CMD), U12.7 (R/#B), U12.33 (NC)
PIN19/NRB1: GPIO-2.35, R73.2, U1.A2 (PC7/NRB1/SDC2_CLK), U12.6 (NC), U12.40 (NC)
PIN20/NDQ0: GPIO-2.37, U1.B3 (PC8/NDQ0/SDC2_D0), U12.29 (I/O0), U12.47 (NC)
PIN21/NDQ1: GPIO-2.39, U1.A3 (PC9/NDQ1/SDC2_D1), U12.30 (I/O1), U12.46 (NC)
PIN22/NDQ2: GPIO-2.40, U1.C4 (PC10/NDQ2/SDC2_D2), U12.31 (I/O2), U12.45 (NC)
PIN23/NDQ3: GPIO-2.38, U1.B4 (PC11/NDQ3/SDC2_D3), U12.27 (NC), U12.32 (I/O3)
PIN24/NDQ4: GPIO-2.36, U1.A4 (PC12/NDQ4/SDC2_D4), U12.41 (I/O4)
PIN25/NDQ5: GPIO-2.34, U1.D5 (PC13/NDQ5/SDC2_D5), U12.42 (I/O5)
PIN26/NDQ6: GPIO-2.32, U1.C5 (PC14/NDQ6/SDC2_D6), U12.43 (I/O6)
PIN27/NDQ7: GPIO-2.30, U1.B5 (PC15/NDQ7/SDC2_D7), U12.44 (I/O7)
PIN28/NWP: GPIO-2.28, U1.A5 (PC16/NWP/UART3_TX)
PIN29: GPIO-2.26, U1.F20 (PE4/TS_D0/CSI_D0/SDC2_DO)
PIN30: GPIO-2.24, U1.F19 (PE5/TS_D1/CSI_D1/SDC2_D1)
PIN31: GPIO-2.22, U1.E20 (PE6/TS_D2/CSI_D2/SDC2_D2)
PIN32: GPIO-2.20, U1.E19 (PE7/TS_D3/CSI_D3/SDC2_D3)
PIN33: GPIO-2.18, U1.D20 (PE8/TS_D4/CSI_D4/SDC2_CMD)
PIN34: GPIO-2.16, U1.D19 (PE9/TS_D5/CSI_D5/SDC2_CLK)
PIN35: GPIO-2.14, U1.C20 (PE10/TS_D6/CSI_D6/UART1_TX)
PIN36: GPIO-2.12, U1.C19 (PE11/TS_D7/CSI_D7/UART1_RX)
PIN37/LED1: GPIO-2.10, R49.1, U1.G19 (PE3/TS_DVLD/CSI_VSYNC/SPI2_MISO)
PIN38: GPIO-2.8, U1.G20 (PE2/TS_SYNC/CSI_HSYNC/SPI2_MOSI)
PIN39: GPIO-2.6, U1.H19 (PE1/TS_ERR/CSI_MCLK/SPI2_CLK/EINT15)
PIN40/UART3-TX: GPIO-1.3, U1.G1 (PG9/SPI1_CS0/UART3_TX/EINT9)
PIN41/UART3-RX: GPIO-1.4, U1.G2 (PG10/SPI1_CLK/UART3_RX/EINT10)
PIN42: GPIO-1.7, U1.D2 (PB5/I2S_MCLK/EINT19)
PIN43: GPIO-1.8, U1.E1 (PB6/I2S_BCLK/EINT20)
PIN44: GPIO-1.9, U1.E2 (PB7/I2S_LRCK/EINT21)
PIN45: GPIO-1.10, U1.F1 (PB8/I2S_DO/EINT22)
PWRON: C124.1, R54.1, U11.2 (PWRON)
RASN: RM14.3.2 (2), U2.F3 (#RAS), U3.F3 (#RAS)
RECOVERY: U1.B11 (PG2/GPS_MAG/EINT2), UBOOT/REC.3
RESET_N: C75.2, GPIO-3.5, JTAG-DEBUG.8, R21.1, T1.1 (B), U1.A8 (RESET_N), U11.33 (PWROK)
RTC-VCC: C113.1, R50.2, U11.18 (RTC31)
SD0-CLK: RM18.4.2 (2), U1.K18 (PF2/SDC0_CLK/UART0_TX)
SD0-CMD: RM18.3.2 (2), U1.K17 (PF3/SDC0_CMD/JTAG_DO1)
SD0-D0: RM19.1.2 (2), U1.L17 (PF1/SDC0_D0/JTAG_DI1)
SD0-D1: RM19.2.2 (2), U1.L18 (PF0/SDC0_D1/JTAG_MS1)
SD0-D2: RM18.1.2 (2), U1.J17 (PF5/SDC0_D2/JTAG_CK1)
SD0-D3: RM18.2.2 (2), U1.J18 (PF4/SDC0_D3/UART0_RX)
SD0-DET#: RM4.1.1 (1), SD/MMC1.10 (CP_E), U1.A10 (PG1/GPS_SIGN/EINT1)
SD1-CLK/UART1_RX: D4.A, R67.1, RM20.1.2 (2), U1.B12 (PG4/SDC1_CLK/MS_CLK/UART1_RX/EINT4)
SD1-CMD/UART1_TX: R27.1, RM20.2.2 (2), U1.A11 (PG3/SDC1_CMD/MS_BS/UART1_TX/EINT3), UART1.2
SD1-D0: RM5.2.1 (1), RM19.3.1 (1), U1.A12 (PG5/SDC1_D0/MS_D0/UART1_CTS/EINT5)
SD1-D1: RM5.3.1 (1), RM19.4.1 (1), U1.B13 (PG6/SDC1_D1/MS_D1/UART1_RTS/UART2_RTS/E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)
SD1-D2: RM5.1.1 (1), RM20.4.2 (2), U1.A13 (PG7/SDC1_D2/MS_D2/UART2_TX/EINT7)
SD1-D3: R25.1, RM20.3.2 (2), U1.B14 (PG8/SDC1_D3/MS_D3/UART2_RX/EINT8)
SD1-DET#: R31.2, RM5.4.1 (1), U1.H3 (PG13/SPI1_CS1/PWM1/UART2_CTS/EINT13)
SD_VCC: C74.2, C76.2, L4.2, SD/MMC1.4 (VDD)
SD_VCC1: C80.2, C83.2, L5.2, SD/MMC2.4 (VDD)
SPI2-CLK/JTAG_CKO: JTAG-DEBUG.3, U1.E4 (PB12/SPI2_CLK/JTAG_CK0/EINT26), UEXT.9
SPI2-CS0/JTAG_MS0: JTAG-DEBUG.2, R44.1, U1.E3 (PB11/SPI2_CS0/JTAG_MS0/EINT25), UEXT.10
SPI2-MISO/JTAG_DI0: JTAG-DEBUG.5, U1.F4 (PB14/SPI2_MISO/JTAG_DI0/EINT28), UEXT.7
SPI2-MOSI/JTAG_DO0: JTAG-DEBUG.4, U1.F3 (PB13/SPI2_MOSI/JTAG_DO0/EINT27), UEXT.8
SVREF: C8.2, C9.2, C49.2, C50.2, R1.1, R3.2, R4.2, U1.L4 (SVREF0), U1.U11 (SVREF1)
TPX1: C89.2, LCD_CON.37, U1.Y20 (TPX1)
TPX2: C90.2, LCD_CON.38, U1.Y19 (TPX2)
TPY1: C91.2, LCD_CON.39, U1.W20 (TPY1)
TPY2: C93.2, LCD_CON.40, U1.W19 (TPY2)
TVOUT: MIC/TV.9, U1.M18 (TVOUT)
TWI2-SCK: R42.1, U1.A7 (PB17/TWI2_SCK), UEXT.5
TWI2-SDA: R43.1, U1.B8 (PB18/TWI2_SDA), UEXT.6
UART0-RX: D3.A, R66.1, U1.G4 (PB20/UART0_RX/EINT30)
UART0-TX: U1.G3 (PB19/UART0_TX/EINT29), UART0.2
UART2-RX: U1.B7 (PC19/NDQS/UART2_RX/UART3_RTS), U12.35 (NC), UEXT.4
UART2-TX: U1.A6 (PC18/NCE3/UART2_TX/UART3_CTS), UEXT.3
UBOOT: U1.A9 (UBOOT_N), UBOOT/REC.1, UBOOT_EN.1
UDM0: U1.P18 (UDM0), USB_OTG.D-
UDM1: U1.N18 (UDM1), USB_HOST.2
UDP0: U1.P17 (UDP0), USB_OTG.D+
UDP1: U1.N17 (UDP1), USB_HOST.3
USB0-DRV: R33.2, U1.H1 (PG11/SPI1_MOSI/UART3_CTS/EINT11), U9.4 (EN)
USB0-IDDET: R41.2, U1.H2 (PG12/SPI1_MISO/UART3_RTS/EINT12), USB_OTG.ID
USB0-VBUSDET: C85.1, R32.1, R35.2, U1.B10 (PG0/GPS_CLK/EINT0)
USB1-DRV: +5V/USB1-DRV.1, U1.D3 (PB10/SPI2_CS1/SPDIF_DO/EINT24)
V12_DLL: C10.2, C11.2, C12.2, R2.1, U1.J4 (VDD_DLL), U1.J5 (VDD_DLL)
V33_HDMI: C97.1, C98.2, R40.2, U1.R16 (V33_HDMI)
V+: 1.5V.1, 1.5V_E.2, C1.2, C2.2, C3.2, C4.2, C5.2, C6.2, C7.2, C8.1, C22.1, C24.2, C25.2, C26.2, C27.2, C28.2, C29.2, C32.2, C33.2, C34.2, C35.2, C36.2, C37.2, R1.2, R5.2, U1.M5 (VCC_DRAM), U1.N5 (VCC_DRAM), U1.T5 (VCC_DRAM), U1.T6 (VCC_DRAM), U1.T9 (VCC_DRAM), U1.T10 (VCC_DRAM), U1.T11 (VCC_DRAM), U2.A2 (VDD), U2.A9 (VDD), U2.B9 (VDDQ), U2.C1 (VDDQ), U2.D7 (VDD), U2.E2 (VDDQ), U2.E9 (VDDQ), U2.G2 (VDD), U2.G8 (VDD), U2.K1 (VDD), U2.K9 (VDD), U2.M1 (VDD), U2.M9 (VDD), U3.A2 (VDD), U3.A9 (VDD), U3.B9 (VDDQ), U3.C1 (VDDQ), U3.D7 (VDD), U3.E2 (VDDQ), U3.E9 (VDDQ), U3.G2 (VDD), U3.G8 (VDD), U3.K1 (VDD), U3.K9 (VDD), U3.M1 (VDD), U3.M9 (VDD)
VCC: 3.3V.1, 3.3V_E.2, C51.2, C52.2, C53.2, C54.2, C55.2, C56.2, C57.2, C84.2, C104.1, C127.2, C128.2, C132.2, D1.A, GPIO-1.1, GPIO-2.3, GPIO-3.3, JTAG-DEBUG.1, L1.2, L2.2, L4.1, L5.1, LAN.AG, LCD_CON.3, R12.1, R13.2, R20.2, R21.2, R23.2, R27.2, R40.1, R41.1, R42.2, R43.2, R44.2, R45.1, R46.2, R47.2, R51.2, R52.2, R55.1, R56.1, R57.1, R66.2, R67.2, R72.1, R73.1, RM1.1.1 (1), RM1.2.1 (1), RM2.1.1 (1), RM4.2.2 (2), RM4.3.2 (2), RM4.4.2 (2), RM5.1.2 (2), RM5.2.2 (2), RM5.3.2 (2), RM5.4.2 (2), U1.E5 (VCC), U1.F5 (VCC), U1.G16 (VCC), U1.H16 (VCC), U1.J16 (VCC), U1.K16 (VCC), U1.L16 (VCC), U1.T14 (V33_HP), U4.37 (ANE), U4.38 (DUPLEX), U4.39 (SPEED), U4.41 (LDPS), U4.44 (MII/SNIB), U5.8 (VCC), U11.10 (DLDOIN), U12.1 (NC), U12.12 (VCC), U12.24 (NC), U12.28 (NC), U12.34 (NC), U12.37 (VCC), U12.39 (NC), UART0.1, UART1.1, UEXT.1, VPS+.2
VCC/2: 1.2V_CPU.1, 1.2V_CPU_E.2, C38.2, C39.2, C40.2, C41.2, C42.2, C43.2, C44.2, C45.2, C46.2, U1.E6 (VDD_CPU), U1.E7 (VDD_CPU), U1.E8 (VDD_CPU), U1.E9 (VDD_CPU), U1.E10 (VDD_CPU), U1.E11 (VDD_CPU), U1.E12 (VDD_CPU), U1.E13 (VDD_CPU), U1.E14 (VDD_CPU)
VCCINT: 1.2V_INT.1, 1.2V_INT_E.2, C13.2, C14.2, C15.2, C16.2, C17.2, C18.2, C19.2, C20.2, C21.2, R2.2, U1.E15 (VDD_CORE), U1.E16 (VDD_CORE), U1.F16 (VDD_CORE), U1.H4 (VDD_CORE), U1.H5 (VDD_CORE), U1.M16 (VDD_CORE), U1.M17 (VDD_CORE), U1.T13 (VDD_CORE), U1.U13 (VDD_CORE)
VMIC: MIC/TV.5, U1.Y16 (VMIC)
VPP: 3.0VA.1, 3.0VA_E.2, C71.2, GPIO-1.13, R18.1, U1.T15 (AVCC)
WEN: RM14.1.2 (2), U2.H3 (#WE), U3.H3 (#WE)
XTALI: C67.2, Q2.2, U1.U20 (X24MIN)
XTALI1: C61.2, Q1.2, U4.46 (X1)
XTALO: C68.2, Q2.1, U1.V20 (X24MOUT)
XTALO1: C62.2, Q1.1, U4.47 (X2)

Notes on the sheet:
POWER SUPPLY CIRCUIT
MicroSD
UEXT
USB-OTG
USB-HOST
GPIO EXTENSIONs
LCD EXTENSION
Ethernet
EEPROM
MAC Address
16 Kbit
(2048 x 8)
HDMI
SD/MMC
Audio In/Out, Mic & Video
LEDs
512Mbytes DDR3 SDRAM (256Mx2)
Debug Interface
JTAG0-SEL JTAG1-SEL FUNCTION
0 0 JTAG port mapping to PF
0 1 JTAG port mapping to PF
1 0 JTAG port mapping to PB
1 1 JTAG port mapping depend on software config
NAND Flash
32Gb (4096M x 8bit)
Buttons
